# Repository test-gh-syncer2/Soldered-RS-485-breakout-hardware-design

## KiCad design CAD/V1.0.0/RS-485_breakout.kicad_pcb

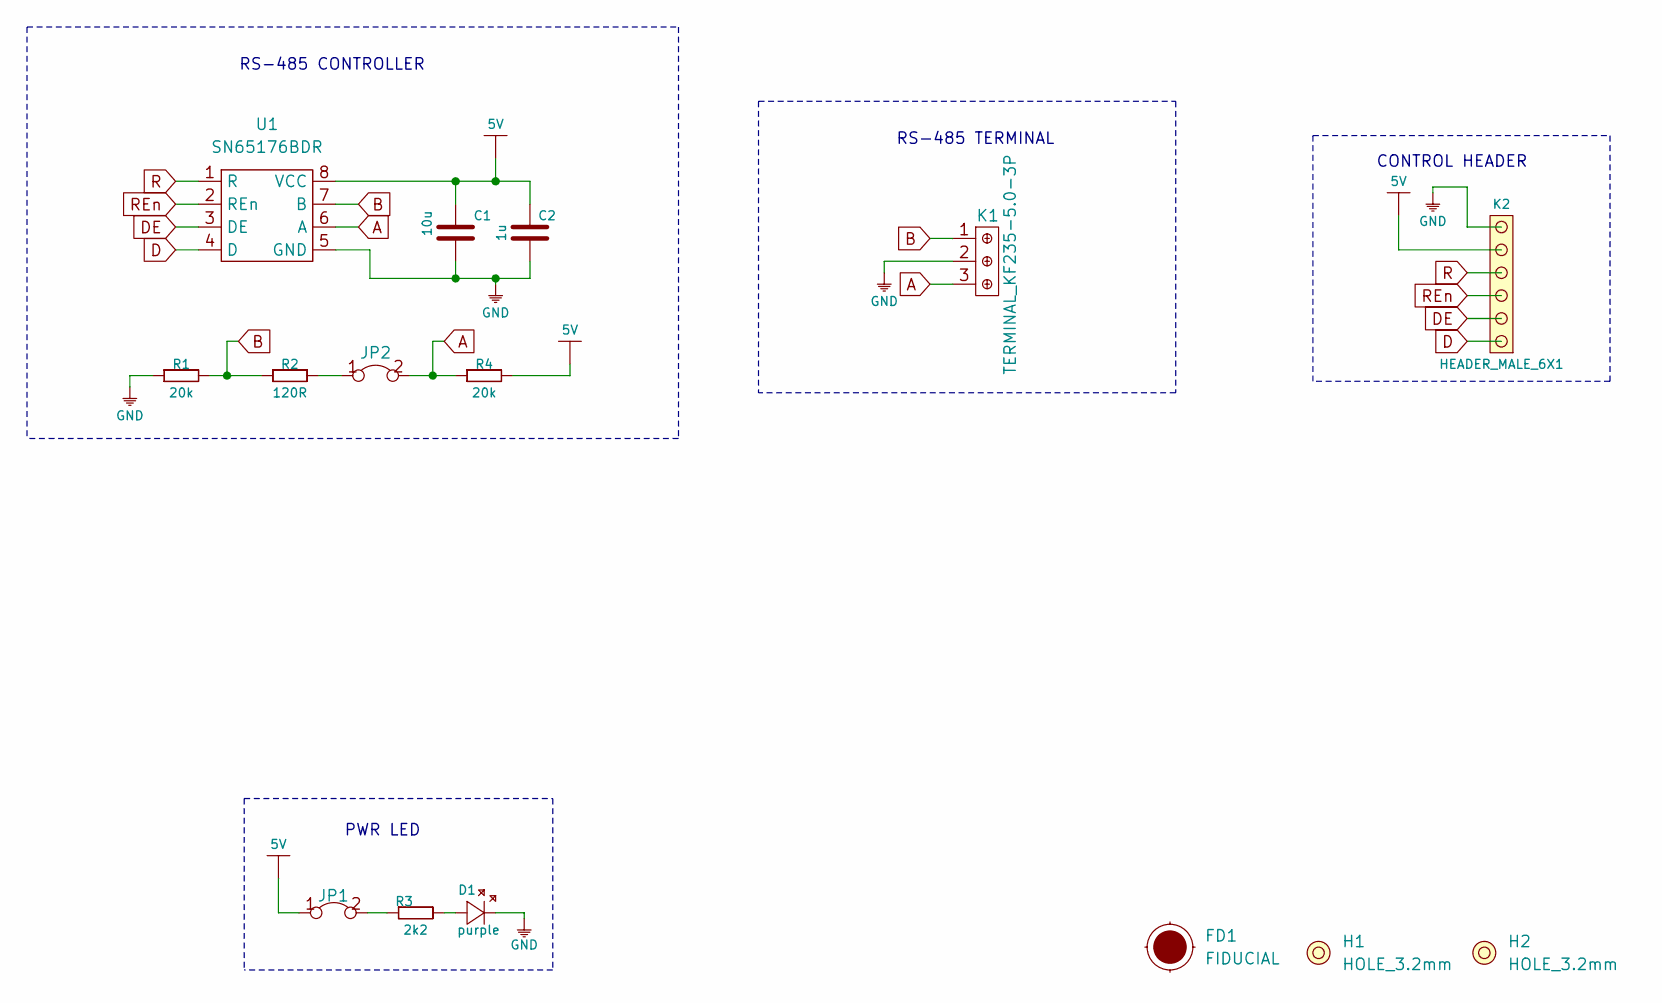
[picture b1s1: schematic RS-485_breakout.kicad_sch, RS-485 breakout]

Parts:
C1: 10u; 1206C
C2: 1u; 0603C
D1: purple; 0402LED
FD1: FIDUCIAL; FIDUCIAL_23
H1, H2: HOLE_3.2mm
JP1: SMD-JUMPER-CONNECTED_TRACE_SLODERMASK
JP2: SMD-JUMPER-CONNECTED; SMD_JUMPER_CONNECTED
K1: TERMINAL_KF235-5.0-3P
K2: HEADER_MALE_6X1
R1, R4: 20k; 0603R
R2: 120R; 0603R
R3: 2k2; 0402R
U1: SN65176BDR; SOIC-8-SWB

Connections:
5V: C1.2, C2.2, JP1.1, K2.5, R4.2, U1.8 (VCC)
A: JP2.2, K1.3, R4.1, U1.6 (A)
B: K1.1, R1.2, R2.1, U1.7 (B)
D: K2.1, U1.4 (D)
DE: K2.2, U1.3 (DE)
GND: C1.1, C2.1, D1.2 (K), K1.2, K2.6, R1.1, U1.5 (GND)
unnamed: D1.1 (A), R3.2
unnamed: JP1.2, R3.1
unnamed: JP2.1, R2.2
R: K2.4, U1.1 (R)
REn: K2.3, U1.2 (REn)

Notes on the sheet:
RS-485 CONTROLLER
PWR LED
RS-485 TERMINAL
CONTROL HEADER

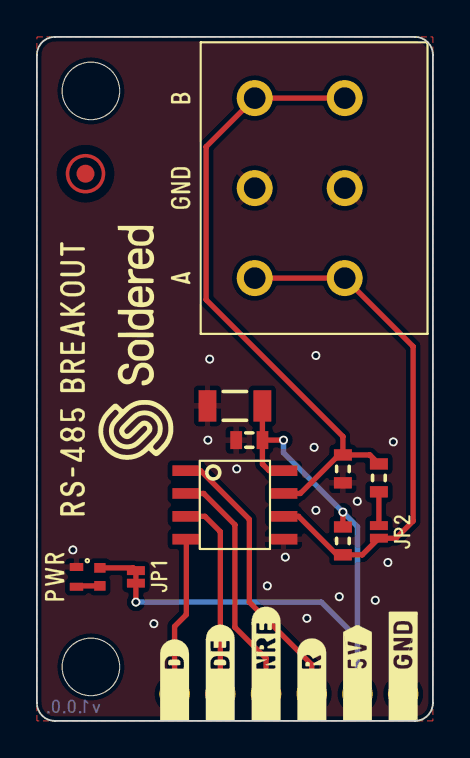
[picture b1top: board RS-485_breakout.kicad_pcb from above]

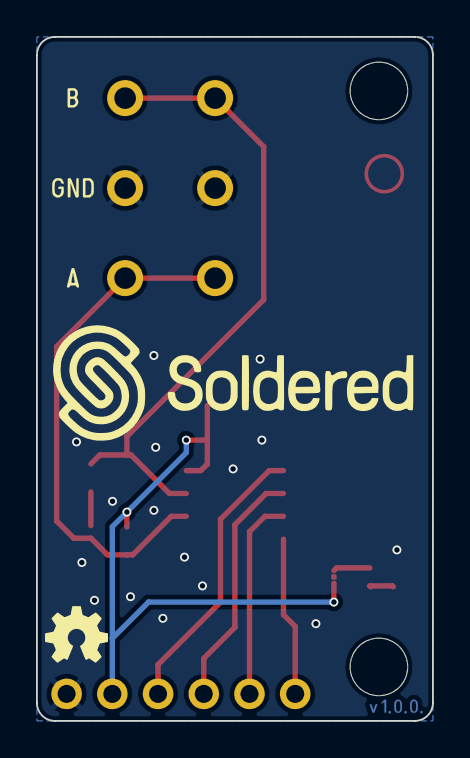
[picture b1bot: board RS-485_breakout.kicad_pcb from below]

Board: 2 copper layers, 22.0 x 38.0 mm, 16 parts (2 on the bottom side), 11 nets.

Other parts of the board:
Ref**: Val**; Version1.0.0.

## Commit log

2021-09-23 Syncing to git
2021-09-23 Updating open source files.
